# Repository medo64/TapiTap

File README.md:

TapiTap
=======

Game of reflexes.

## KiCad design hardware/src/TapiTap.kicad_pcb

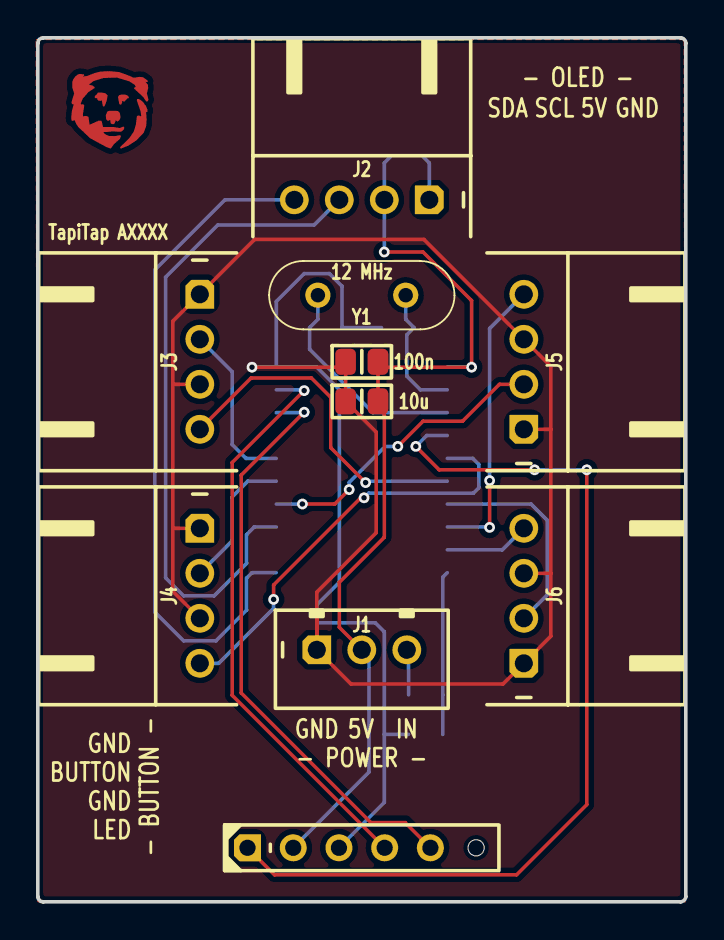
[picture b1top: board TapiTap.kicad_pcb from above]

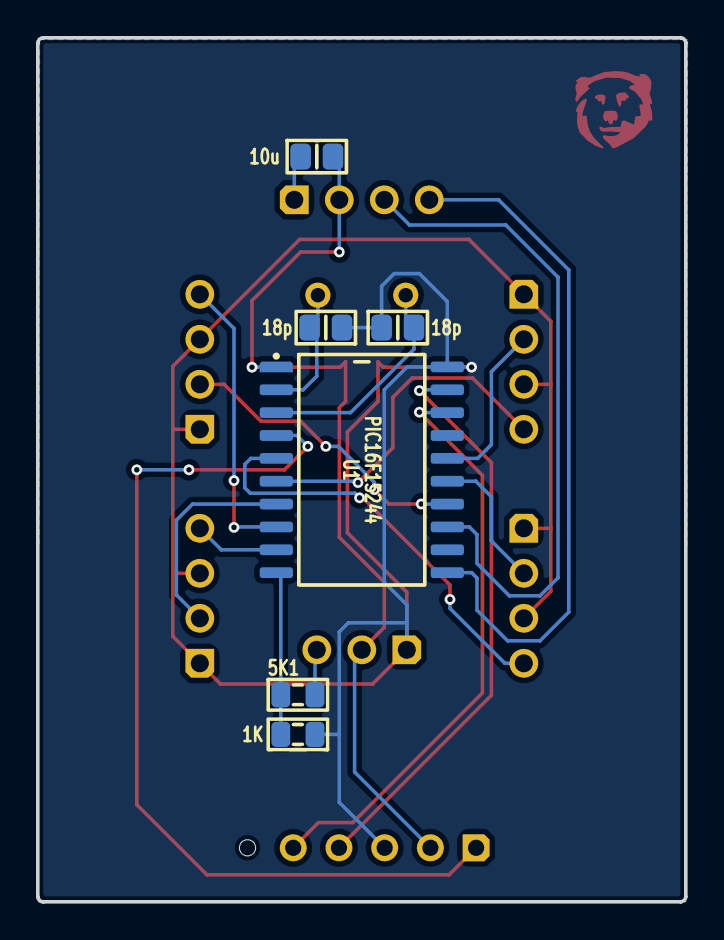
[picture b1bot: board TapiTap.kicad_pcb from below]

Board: 2 copper layers, 36.0 x 48.0 mm, 17 parts (6 on the bottom side), 19 nets.

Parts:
C1, C2: 18p; C (0805)
C3: 100n; C (0805)
C4, C5: 10u; C (0805)
ICON: Medo64; ICON Medo64
ICSP: Microchip PIC; ICSP PIC Pogo (6w)
J1: S4B-XH-A; J JST XH B (3w)
J2, J3, J4, J5, J6: S4B-XH-A; J JST XH S (4w)
R1: 1K; R (0805)
R2: 5K1; R (0805)
U1: PIC16F15244; U Micro [PIC16F15244] (SOIC-20)
Y1: 12 MHz; Y Crystal (HC49U)

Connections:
5V: C3.2, C4.2, C5.1, ICSP.2, J1.2, J2.2, U1.1
GND: C1.2, C2.2, C3.1, C4.1, C5.2, ICSP.3, J1.1, J2.1, J3.1, J3.3, J4.1, J4.3, J5.1, J5.3, J6.1, J6.3, R1.2, U1.20
ICSP_DAT: ICSP.4, U1.19
ICSP_VPP: ICSP.1, U1.4
IN_ADC_BAT: R1.1, R2.2, U1.10
IN_BUTTON1: J3.2, U1.16
IN_BUTTON2: J4.2, U1.15
IN_BUTTON3: J5.2, U1.14
IN_BUTTON4: J6.2, U1.7
IN_Vinput: J1.3, R2.1
ISCP_CLK: ICSP.5, U1.18
OSC1: C1.1, U1.2, Y1.1
OSC2: C2.1, U1.3, Y1.2
OUT_LED1: J3.4, U1.6
OUT_LED2: J4.4, U1.5
OUT_LED3: J5.4, U1.8
OUT_LED4: J6.4, U1.9
SCL: J2.3, U1.13
SDA: J2.4, U1.11
